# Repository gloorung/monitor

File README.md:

TFT Status Monitor

Eagle Files for:
- Raspberry Pi: rfm12pi v1 and 1.8"tft
- BeagleBone Black: rfm12pi v1, 1.8"tft and 2 push buttons

Python code adapted from script by Martin Harizanov (harizanov.com)

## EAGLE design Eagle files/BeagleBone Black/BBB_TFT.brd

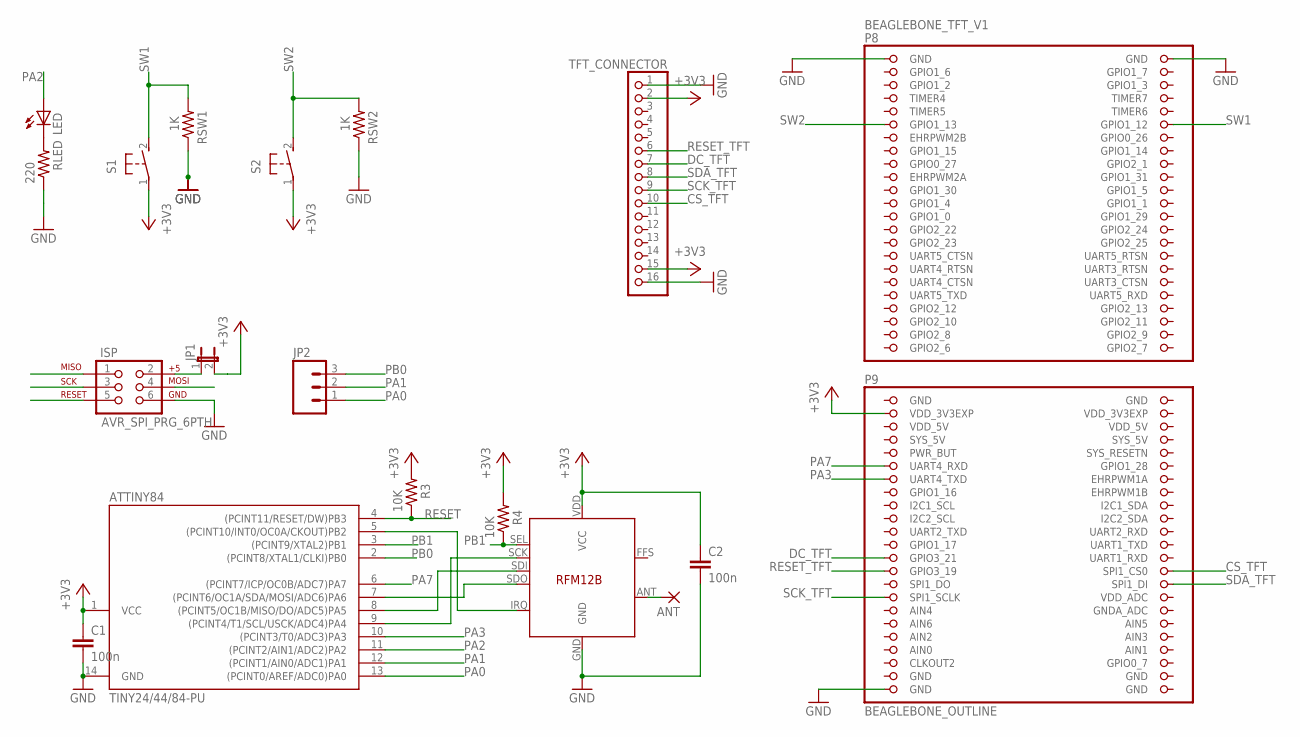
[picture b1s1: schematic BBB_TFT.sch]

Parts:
ANT: 1,6/0,8
ATTINY84: TINY24/44/84-PU; DIL14
BEAGLEBONE_TFT_V1: BEAGLEBONE_OUTLINE; BEAGLEBONE_SHIELD
C1, C2: 100n; C025-024X044
ISP: AVR_SPI_PRG_6PTH; 2X3
JP1: JUMPER-2PTH; 1X02
JP2: M03LOCK; 1X03_LOCK
LED: LED5MM
R3, R4: 10K; AXIAL-0.3
RFM12B: RFM12B
RLED: 220; AXIAL-0.3
RSW1, RSW2: 1K; AXIAL-0.3
S1, S2: 31-XX; B3F-31XX
TFT_CONNECTOR: PINHD-1X16; 1X16

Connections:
+3V3: ATTINY84.1 (VCC), BEAGLEBONE_TFT_V1.49 (VDD_3V3EXP), C1.1, C2.1, JP1.2, R3.P$2 (2), R4.P$2 (2), RFM12B.VDD (VCC), S1.1, S2.1, TFT_CONNECTOR.2, TFT_CONNECTOR.15
AIN0: BEAGLEBONE_TFT_V1.85 (AIN0)
CS_TFT: BEAGLEBONE_TFT_V1.74 (SPI1_CS0), TFT_CONNECTOR.10
DC_TFT: BEAGLEBONE_TFT_V1.71 (GPIO3_21), TFT_CONNECTOR.7
GND: ATTINY84.14 (GND), BEAGLEBONE_TFT_V1.1 (GND), BEAGLEBONE_TFT_V1.2 (GND), BEAGLEBONE_TFT_V1.47 (GND), BEAGLEBONE_TFT_V1.48 (GND), BEAGLEBONE_TFT_V1.89 (GND), BEAGLEBONE_TFT_V1.90 (GND), BEAGLEBONE_TFT_V1.91 (GND), BEAGLEBONE_TFT_V1.92 (GND), C1.2, C2.2, ISP.6, RFM12B.GND, RLED.P$1 (1), RSW1.P$1 (1), RSW2.P$1 (1), TFT_CONNECTOR.1, TFT_CONNECTOR.16
MISO: ATTINY84.8 ((PCINT5/OC1B/MISO/DO/ADC5)PA5), ISP.1, RFM12B.SDI
MOSI: ATTINY84.7 ((PCINT6/OC1A/SDA/MOSI/ADC6)PA6), ISP.4, RFM12B.SDO
unnamed: ISP.2, JP1.1
unnamed: LED.K (C), RLED.P$2 (2)
unnamed: ANT.1, RFM12B.ANT
PA0: ATTINY84.13 ((PCINT0/AREF/ADC0)PA0), JP2.1
PA1: ATTINY84.12 ((PCINT1/AIN0/ADC1)PA1), JP2.2
PA2: ATTINY84.11 ((PCINT2/AIN1/ADC2)PA2), LED.A
PA3: ATTINY84.10 ((PCINT3/T0/ADC3)PA3), BEAGLEBONE_TFT_V1.59 (UART4_TXD)
PA7: ATTINY84.6 ((PCINT7/ICP/OC0B/ADC7)PA7), BEAGLEBONE_TFT_V1.57 (UART4_RXD)
PB0: ATTINY84.2 ((PCINT8/XTAL1/CLKI)PB0), JP2.3
PB1: ATTINY84.3 ((PCINT9/XTAL2)PB1), R4.P$1 (1), RFM12B.SEL
PB2: ATTINY84.5 ((PCINT10/INT0/OC0A/CKOUT)PB2), RFM12B.IRQ
RESET: ATTINY84.4 ((PCINT11/RESET/DW)PB3), ISP.5, R3.P$1 (1)
RESET_TFT: BEAGLEBONE_TFT_V1.73 (GPIO3_19), TFT_CONNECTOR.6
SCK: ATTINY84.9 ((PCINT4/T1/SCL/USCK/ADC4)PA4), ISP.3, RFM12B.SCK
SCK_TFT: BEAGLEBONE_TFT_V1.77 (SPI1_SCLK), TFT_CONNECTOR.9
SDA_TFT: BEAGLEBONE_TFT_V1.76 (SPI1_DI), TFT_CONNECTOR.8
SW1: BEAGLEBONE_TFT_V1.12 (GPIO1_12), RSW1.P$2 (2), S1.2 (S)
SW2: BEAGLEBONE_TFT_V1.11 (GPIO1_13), RSW2.P$2 (2), S2.2 (S)
SYS_5V: BEAGLEBONE_TFT_V1.53 (SYS_5V)
VDD_3V3EXP: BEAGLEBONE_TFT_V1.50 (VDD_3V3EXP)
VDD_5V: BEAGLEBONE_TFT_V1.51 (VDD_5V), BEAGLEBONE_TFT_V1.52 (VDD_5V)

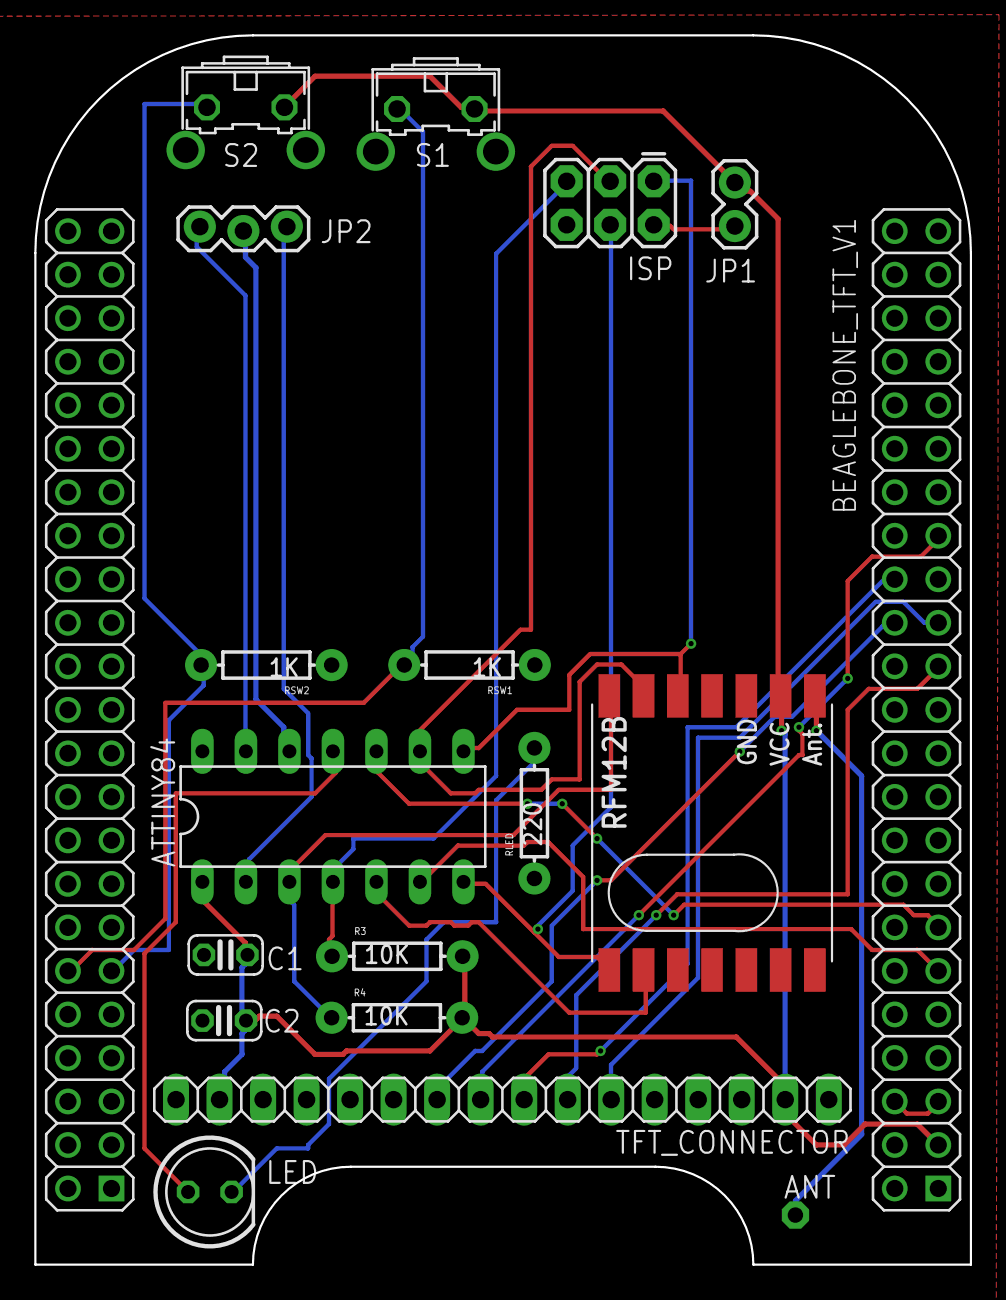
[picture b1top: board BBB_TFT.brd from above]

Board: 2 copper layers, 54.6 x 71.8 mm, 18 parts (0 on the bottom side), 25 nets.

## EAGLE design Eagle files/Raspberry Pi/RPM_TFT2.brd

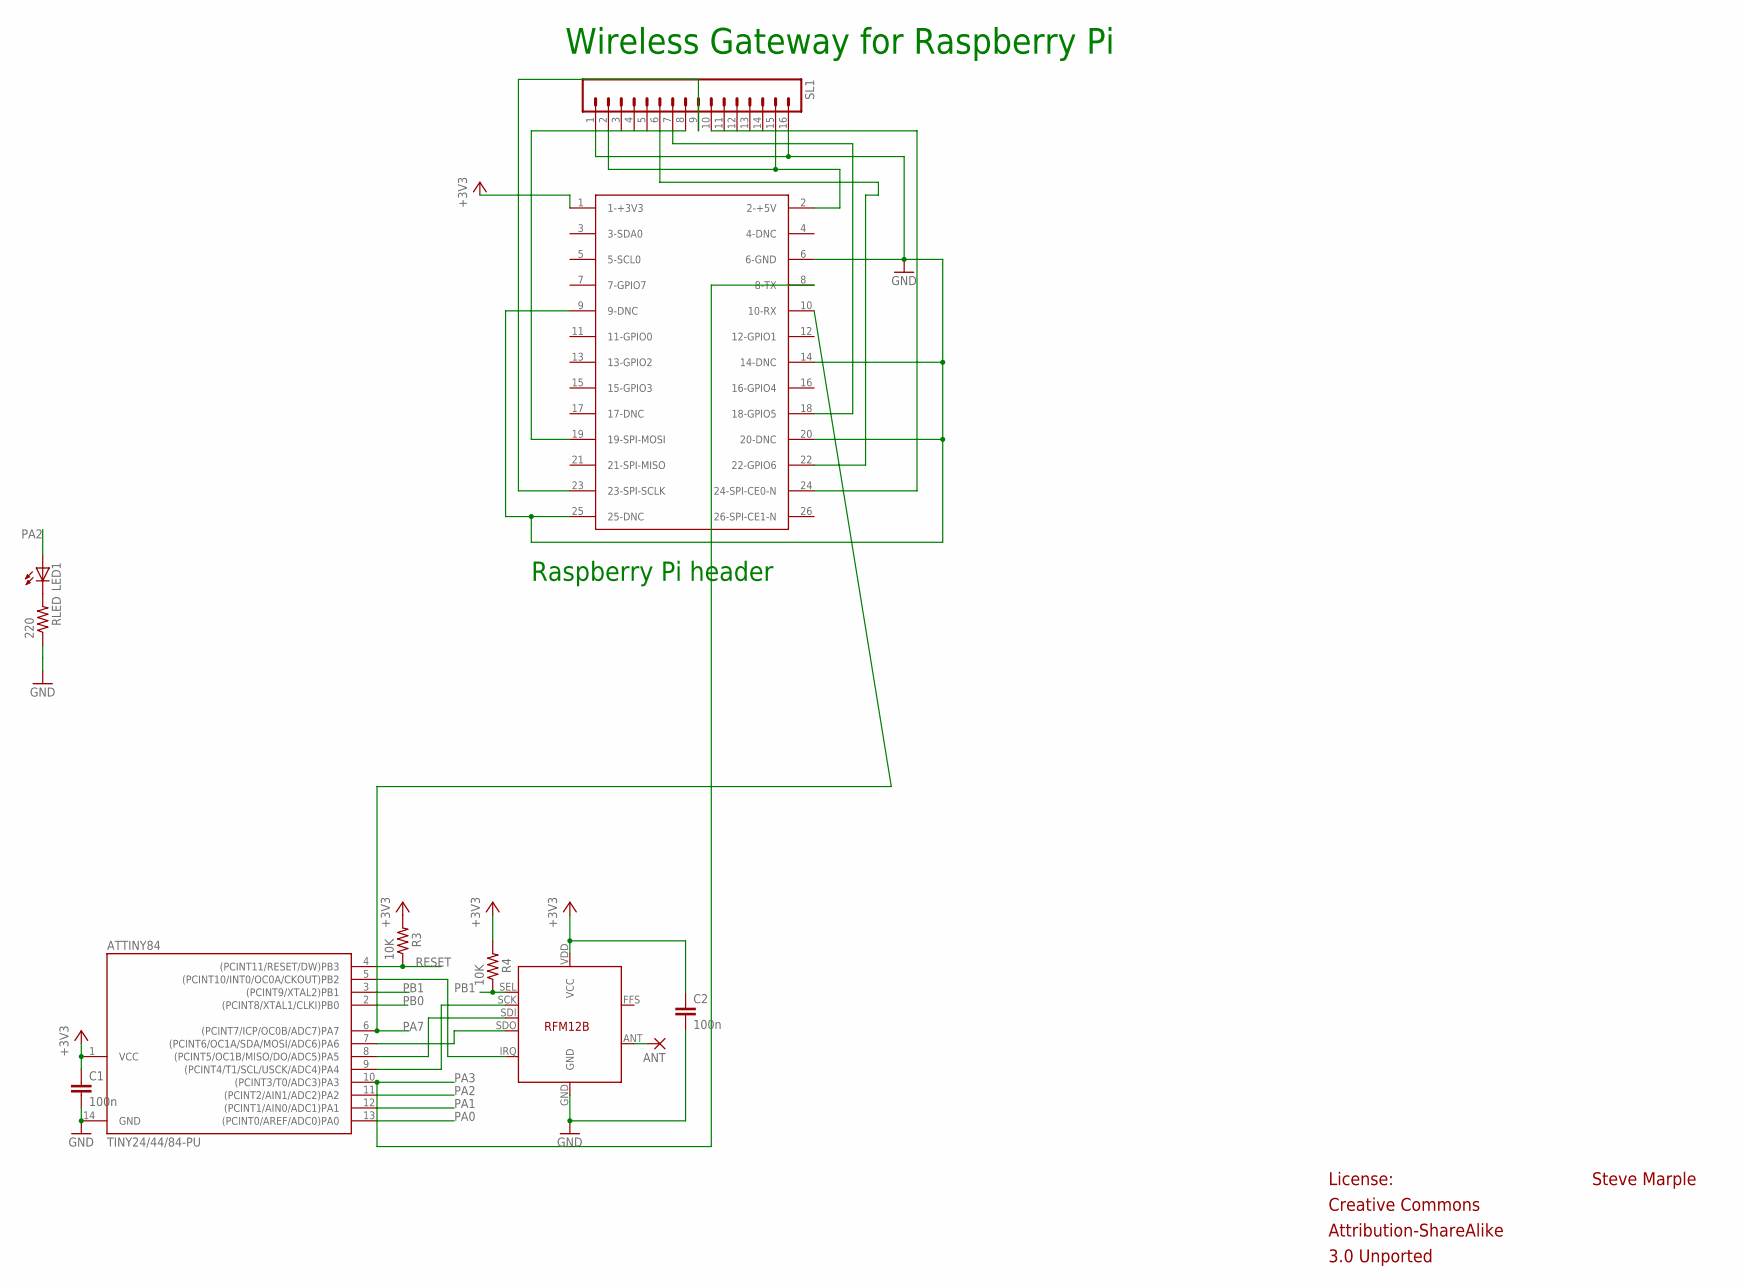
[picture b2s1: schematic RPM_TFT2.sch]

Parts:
ANT: 1,6/0,8
ATTINY84: TINY24/44/84-PU; DIL14
C1, C2: 100n; C025-024X044
LED1: LED5MM
R3, R4: 10K; AXIAL-0.3
RFM12B: RFM12B
RLED: 220; AXIAL-0.3
SL1: M16; 16P
X1: P1A; RASPBERRY-PI-HEADER

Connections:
+3V3: ATTINY84.1 (VCC), C1.1, C2.1, R3.P$2 (2), R4.P$2 (2), RFM12B.VDD (VCC), X1.1 (1-+3V3)
GND: ATTINY84.14 (GND), C1.2, C2.2, RFM12B.GND, RLED.P$1 (1), SL1.1, SL1.16, X1.6 (6-GND), X1.9 (9-DNC), X1.14 (14-DNC), X1.20 (20-DNC), X1.25 (25-DNC)
MISO: ATTINY84.8 ((PCINT5/OC1B/MISO/DO/ADC5)PA5), RFM12B.SDI
MOSI: ATTINY84.7 ((PCINT6/OC1A/SDA/MOSI/ADC6)PA6), RFM12B.SDO
unnamed: SL1.6, X1.22 (22-GPIO6)
unnamed: LED1.K (C), RLED.P$2 (2)
unnamed: SL1.2, SL1.15, X1.2 (2-+5V)
unnamed: SL1.7, X1.18 (18-GPIO5)
unnamed: ANT.1, RFM12B.ANT
unnamed: SL1.8, X1.19 (19-SPI-MOSI)
unnamed: SL1.9, X1.23 (23-SPI-SCLK)
unnamed: SL1.10, X1.24 (24-SPI-CE0-N)
PA0: ATTINY84.13 ((PCINT0/AREF/ADC0)PA0)
PA1: ATTINY84.12 ((PCINT1/AIN0/ADC1)PA1)
PA2: ATTINY84.11 ((PCINT2/AIN1/ADC2)PA2), LED1.A
PA3: ATTINY84.10 ((PCINT3/T0/ADC3)PA3), X1.8 (8-TX)
PA7: ATTINY84.6 ((PCINT7/ICP/OC0B/ADC7)PA7), X1.10 (10-RX)
PB0: ATTINY84.2 ((PCINT8/XTAL1/CLKI)PB0)
PB1: ATTINY84.3 ((PCINT9/XTAL2)PB1), R4.P$1 (1), RFM12B.SEL
PB2: ATTINY84.5 ((PCINT10/INT0/OC0A/CKOUT)PB2), RFM12B.IRQ
RESET: ATTINY84.4 ((PCINT11/RESET/DW)PB3), R3.P$1 (1)
SCK: ATTINY84.9 ((PCINT4/T1/SCL/USCK/ADC4)PA4), RFM12B.SCK

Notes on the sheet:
Raspberry Pi header
Wireless Gateway for Raspberry Pi
Steve Marple
Creative Commons
Attribution-ShareAlike
3.0 Unported
License:

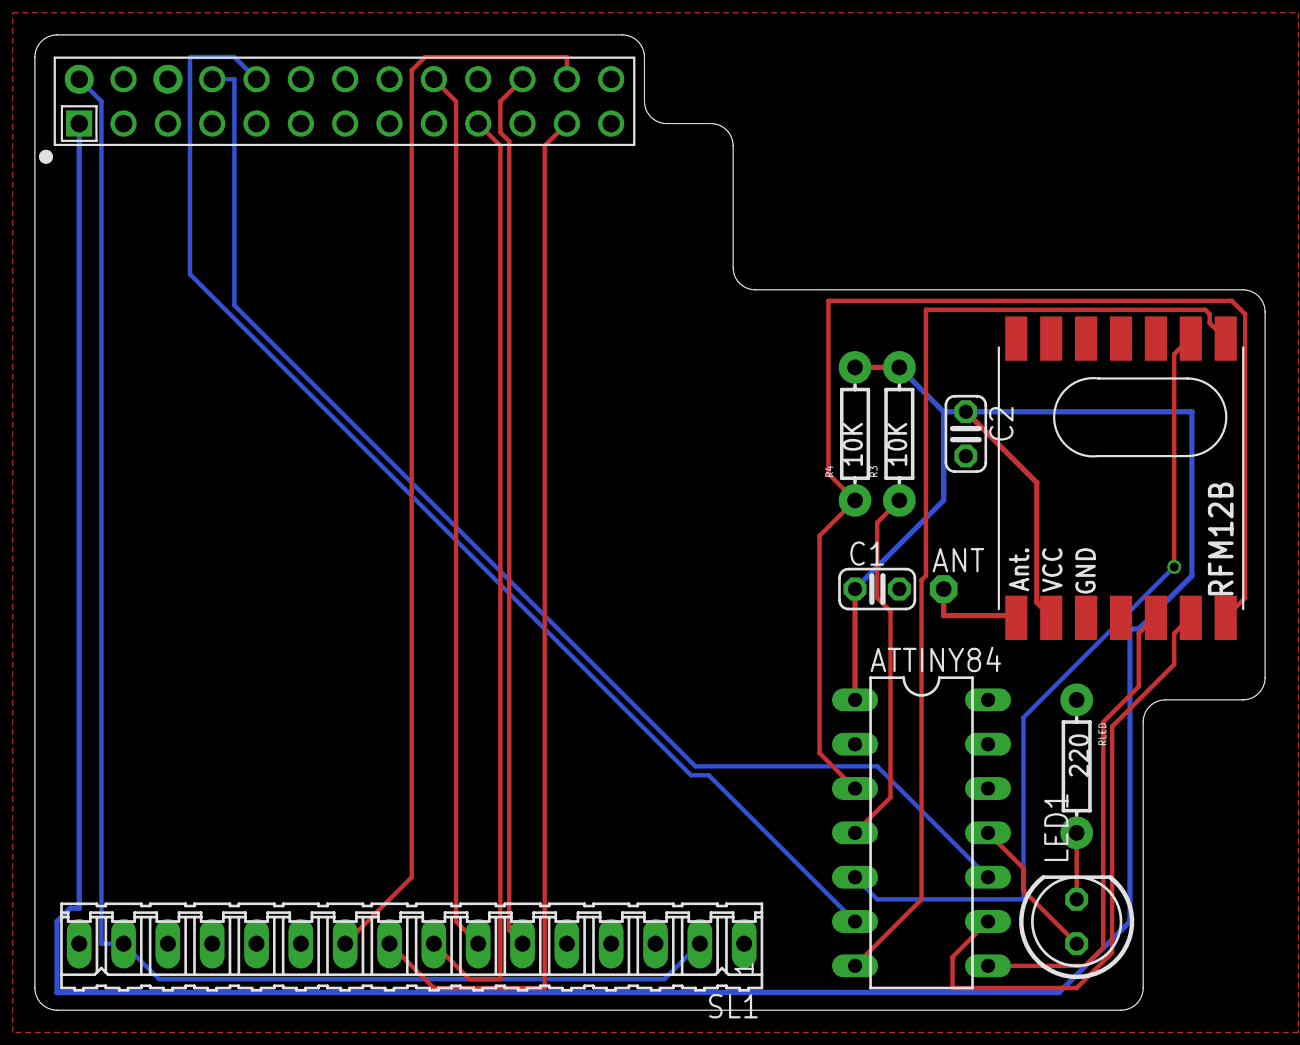
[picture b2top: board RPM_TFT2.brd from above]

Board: 2 copper layers, 70.5 x 55.9 mm, 11 parts (0 on the bottom side), 19 nets.
